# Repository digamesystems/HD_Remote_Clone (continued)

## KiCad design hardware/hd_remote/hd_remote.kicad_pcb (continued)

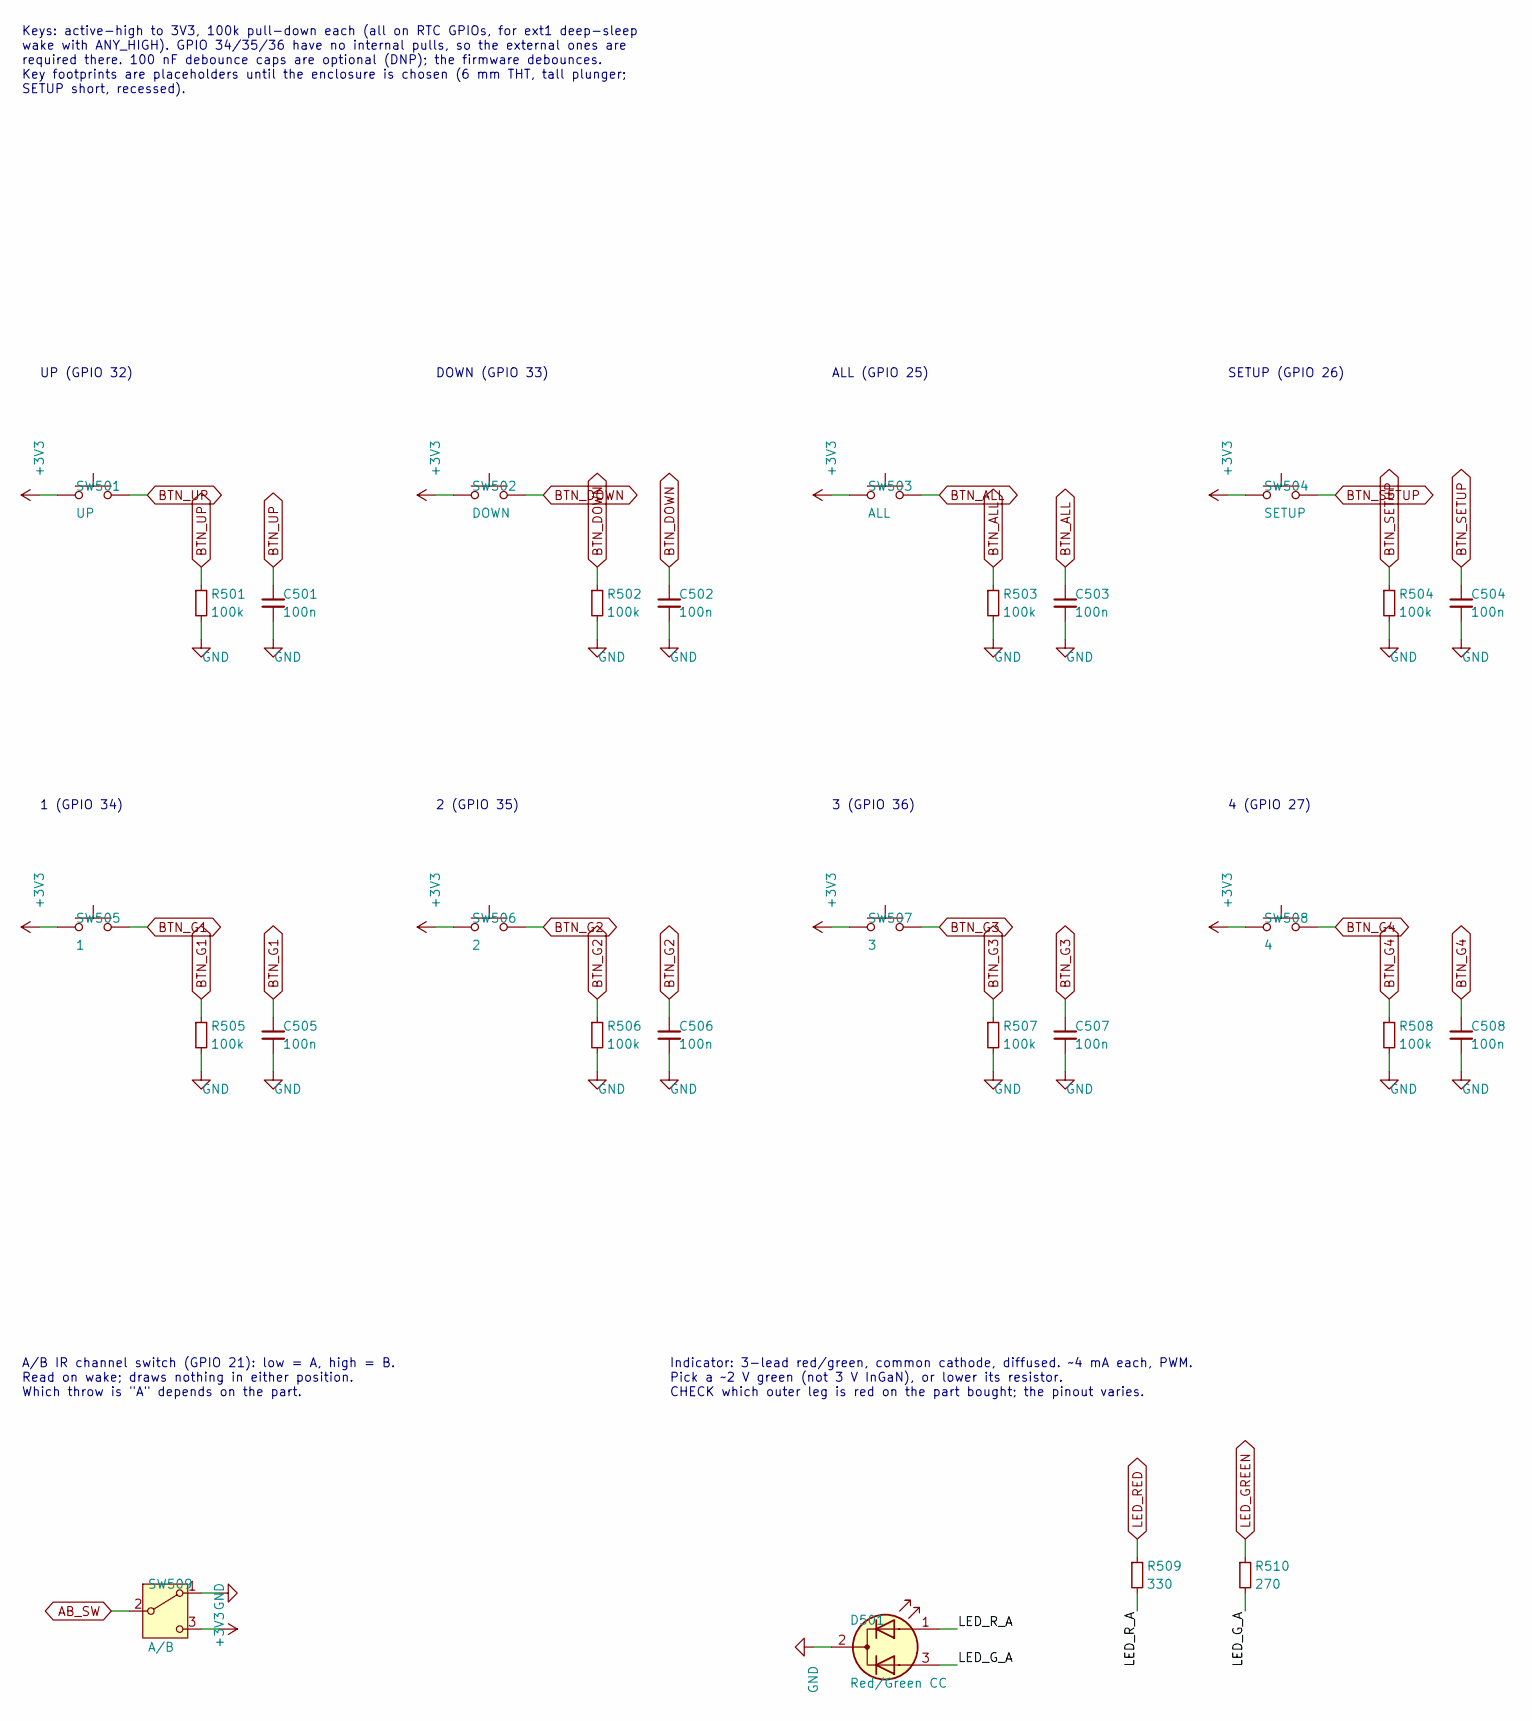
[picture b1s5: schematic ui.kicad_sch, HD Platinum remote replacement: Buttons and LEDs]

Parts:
C501, C502, C503, C504, C505, C506, C507, C508: 100n; C_0603_1608Metric; LCSC C14663
D501: Red/Green CC; LED_D5.0mm-3; MPN WP59EGW
R501, R502, R503, R504, R505, R506, R507, R508: 100k; R_0603_1608Metric; LCSC C25803
R509: 330; R_0603_1608Metric; LCSC C23138
R510: 270; R_0603_1608Metric; LCSC C22966
SW501: UP; SW_PUSH_6mm_H13mm; MPN TS02-66-130-BK-160-SCR-D
SW502: DOWN; SW_PUSH_6mm_H13mm; MPN TS02-66-130-BK-160-SCR-D
SW503: ALL; SW_PUSH_6mm_H13mm; MPN TS02-66-130-BK-160-SCR-D
SW504: SETUP; SW_PUSH_6mm_H5mm; MPN TS02-66-50-BK-160-SCR-D
SW505: 1; SW_PUSH_6mm_H13mm; MPN TS02-66-130-BK-160-SCR-D
SW506: 2; SW_PUSH_6mm_H13mm; MPN TS02-66-130-BK-160-SCR-D
SW507: 3; SW_PUSH_6mm_H13mm; MPN TS02-66-130-BK-160-SCR-D
SW508: 4; SW_PUSH_6mm_H13mm; MPN TS02-66-130-BK-160-SCR-D
SW509: A/B; SW_SPDT_PCM12; LCSC C221841

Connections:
+3V3: SW501.1, SW502.1, SW503.1, SW504.1, SW505.1, SW506.1, SW507.1, SW508.1, SW509.3 (C); also elsewhere on the board
/Buttons and LEDs/LED_G_A: D501.3 (A2), R510.2
/Buttons and LEDs/LED_R_A: D501.1 (A1), R509.2
AB_SW: SW509.2 (B); also elsewhere on the board
BTN_ALL: C503.1, R503.1, SW503.2; also elsewhere on the board
BTN_DOWN: C502.1, R502.1, SW502.2; also elsewhere on the board
BTN_G1: C505.1, R505.1, SW505.2; also elsewhere on the board
BTN_G2: C506.1, R506.1, SW506.2; also elsewhere on the board
BTN_G3: C507.1, R507.1, SW507.2; also elsewhere on the board
BTN_G4: C508.1, R508.1, SW508.2; also elsewhere on the board
BTN_SETUP: C504.1, R504.1, SW504.2; also elsewhere on the board
BTN_UP: C501.1, R501.1, SW501.2; also elsewhere on the board
GND: C501.2, C502.2, C503.2, C504.2, C505.2, C506.2, C507.2, C508.2, D501.2 (K), R501.2, R502.2, R503.2, R504.2, R505.2, R506.2, R507.2, R508.2, SW509.1 (A); also elsewhere on the board
LED_GREEN: R510.1; also elsewhere on the board
LED_RED: R509.1; also elsewhere on the board

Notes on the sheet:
A/B IR channel switch (GPIO 21): low = A, high = B. Read on wake; draws nothing in either position. Which throw is "A" depends on the part.
2 (GPIO 35)
Indicator: 3-lead red/green, common cathode, diffused. ~4 mA each, PWM. Pick a ~2 V green (not 3 V InGaN), or lower its resistor. CHECK which outer leg is red on the part bought; the pinout varies.
1 (GPIO 34)
Keys: active-high to 3V3, 100k pull-down each (all on RTC GPIOs, for ext1 deep-sleep wake with ANY_HIGH). GPIO 34/35/36 have no internal pulls, so the external ones are required there. 100 nF debounce caps are optional (DNP); the firmware debounces. Key footprints are placeholders until the enclosu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
DOWN (GPIO 33)
3 (GPIO 36)
UP (GPIO 32)
SETUP (GPIO 26)
4 (GPIO 27)
ALL (GPIO 25)

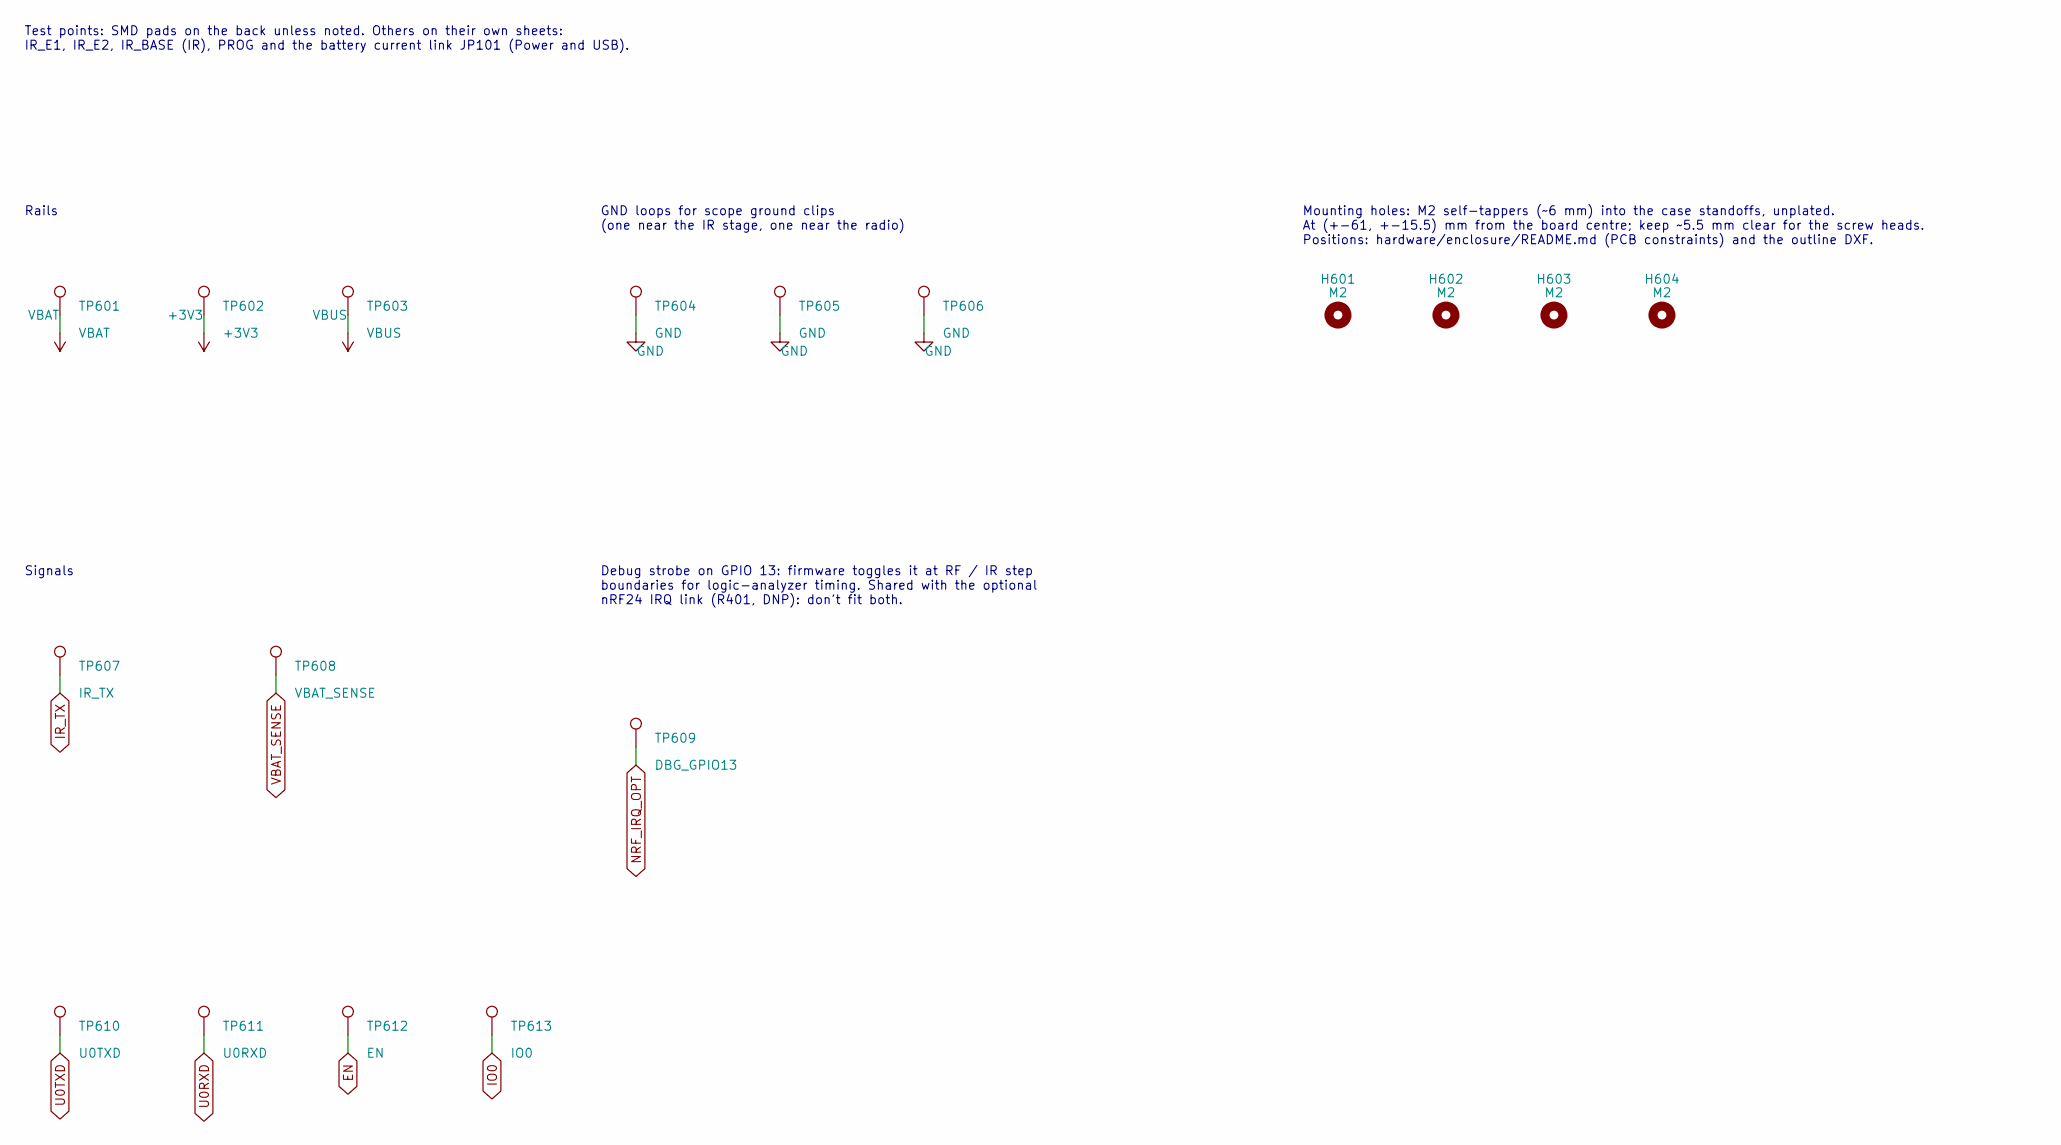
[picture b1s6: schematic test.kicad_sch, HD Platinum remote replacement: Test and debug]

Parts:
H601, H602, H603, H604: M2; MountingHole_2.2mm_M2
TP601: VBAT; TestPoint_Pad_D1.5mm
TP602: +3V3; TestPoint_Pad_D1.5mm
TP603: VBUS; TestPoint_Pad_D1.5mm
TP604, TP605, TP606: GND; TestPoint_Keystone_5000-5004_Miniature
TP607: IR_TX; TestPoint_Pad_D1.5mm
TP608: VBAT_SENSE; TestPoint_Pad_D1.5mm
TP609: DBG_GPIO13; TestPoint_Pad_D1.5mm
TP610: U0TXD; TestPoint_Pad_D1.5mm
TP611: U0RXD; TestPoint_Pad_D1.5mm
TP612: EN; TestPoint_Pad_D1.5mm
TP613: IO0; TestPoint_Pad_D1.5mm

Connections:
+3V3: TP602.1 (1_1); also elsewhere on the board
EN: TP612.1 (1_1); also elsewhere on the board
GND: TP604.1 (1_1), TP605.1 (1_1), TP606.1 (1_1); also elsewhere on the board
IO0: TP613.1 (1_1); also elsewhere on the board
IR_TX: TP607.1 (1_1); also elsewhere on the board
NRF_IRQ_OPT: TP609.1 (1_1); also elsewhere on the board
U0RXD: TP611.1 (1_1); also elsewhere on the board
U0TXD: TP610.1 (1_1); also elsewhere on the board
VBAT: TP601.1 (1_1); also elsewhere on the board
VBAT_SENSE: TP608.1 (1_1); also elsewhere on the board
VBUS: TP603.1 (1_1); also elsewhere on the board

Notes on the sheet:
Signals
GND loops for scope ground clips (one near the IR stage, one near the radio)
Debug strobe on GPIO 13: firmware toggles it at RF / IR step boundaries for logic-analyzer timing. Shared with the optional nRF24 IRQ link (R401, DNP): don't fit both.
Rails
Test points: SMD pads on the back unless noted. Others on their own sheets: IR_E1, IR_E2, IR_BASE (IR), PROG and the battery current link JP101 (Power and USB).
Mounting holes: M2 self-tappers (~6 mm) into the case standoffs, unplated. At (+-61, +-15.5) mm from the board centre; keep ~5.5 mm clear for the screw heads. Positions: hardware/enclosure/README.md (PCB constraints) and the outline DXF.

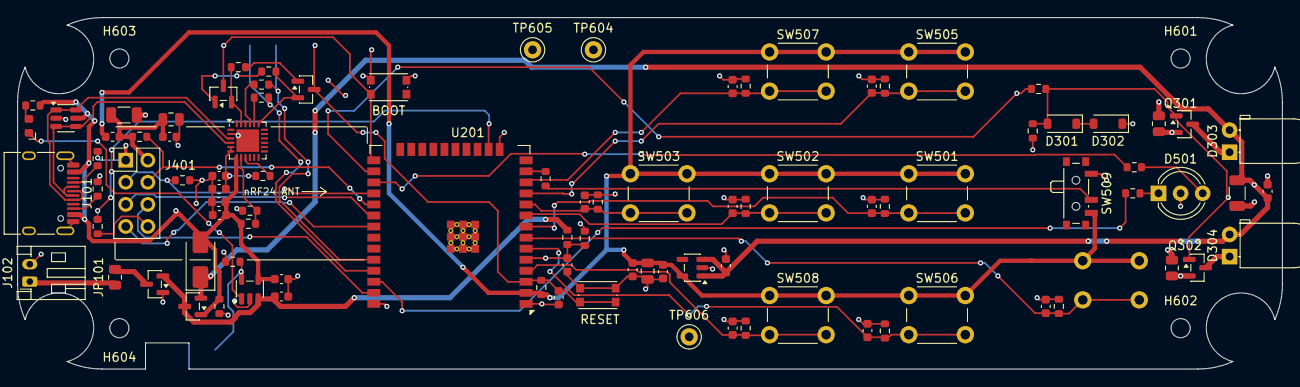
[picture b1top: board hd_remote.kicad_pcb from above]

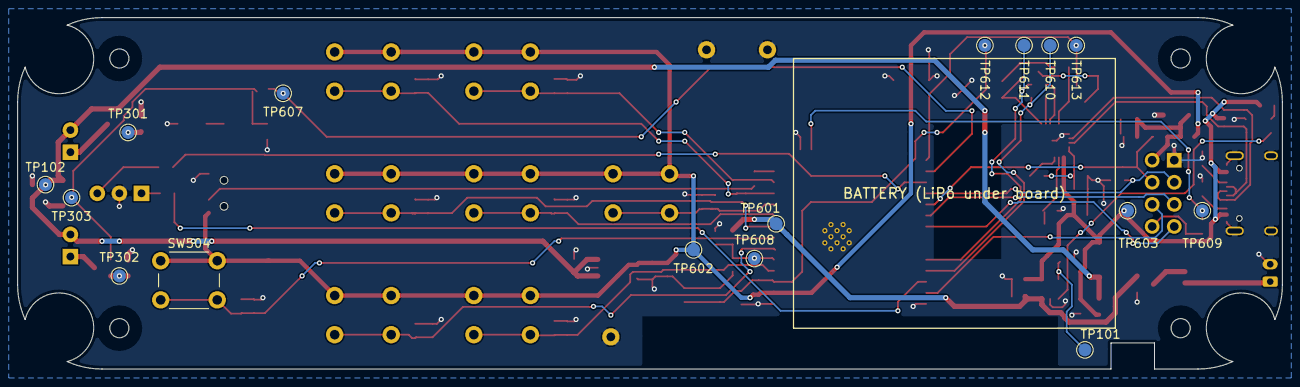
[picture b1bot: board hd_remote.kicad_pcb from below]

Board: 2 copper layers, 145.4 x 40.4 mm, 114 parts (16 on the bottom side), 57 nets.

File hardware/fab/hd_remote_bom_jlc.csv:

Comment,Designator,Footprint,LCSC Part #
4.7u,"C101,C103,C105,C106",C_0603_1608Metric,C19666
100n,"C102,C104,C109,C202,C302,C402,C501,C502,C503,C504,C505,C506,C507,C508",C_0603_1608Metric,C14663
1u,"C107,C108,C203",C_0603_1608Metric,C15849
22u,C201,C_0805_2012Metric,C45783
100u,C301,C_1206_3216Metric,C15008
10u,C401,C_0805_2012Metric,C15850
CHG,D101,LED_Kingbright_APA1606_1.6x0.6mm_Horizontal,C3034753
STPS1H100AY,D102,D_SMA,C181833
1N4148W,"D301,D302",D_SOD-123,C81598
0R (or bead),FB401,L_0603_1608Metric,C21189
USB_C_Receptacle,J101,USB_C_Receptacle_HRO_TYPE-C-31-M-12,C165948
0R,JP101,R_0805_2012Metric,C17477
MMBT3904,"Q101,Q102",SOT-23,C20526
AO3401A,"Q103,Q104",SOT-23,C15127
BC817-40,"Q301,Q302",SOT-23,C52801
5.1k,"R101,R102",R_0603_1608Metric,C23186
1k,"R103,R106,R111",R_0603_1608Metric,C21190
22k,R104,R_0603_1608Metric,C31850
47k,R105,R_0603_1608Metric,C25819
10k,"R107,R108,R109,R201,R202",R_0603_1608Metric,C25804
3.9k,R110,R_0603_1608Metric,C23018
1M,"R112,R113",R_0603_1608Metric,C22935
100k,"R114,R302,R402,R403,R501,R502,R503,R504,R505,R506,R507,R508",R_0603_1608Metric,C25803
470,R301,R_0603_1608Metric,C23179
3.3,"R303,R304",R_0805_2012Metric,C2907250
330,R509,R_0603_1608Metric,C23138
270,R510,R_0603_1608Metric,C22966
RESET/BOOT,"SW201,SW202",SW_Push_1P1T_NO_CK_KMR2,C269272
A/B,SW509,SW_SPDT_PCM12,C221841
USBLC6-2SC6,U101,SOT-23-6,C7519
CP2102N-A02-GQFN24,U102,QFN-24-1EP_4x4mm_P0.5mm_EP2.6x2.6mm,C969151
MCP73831-2-OT,U103,SOT-23-5,C424093
RT9080-33GJ5,U104,SOT-23-5,C841192
ESP32-WROOM-32E,U201,ESP32-WROOM-32E,C701341

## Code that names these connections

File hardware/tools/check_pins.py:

# SPDX-License-Identifier: GPL-2.0-or-later
"""Check the firmware's handheld pin map (include/pins.h) against the KiCad design.

Exports the schematic netlist with kicad-cli, reads which net each ESP32 module pin (U201) is on,
converts module pins to GPIO numbers, and compares that with every PIN_ constant in the
HD_BOARD_HANDHELD block of include/pins.h. Also reports ESP32 signal nets that pins.h doesn't name.

  python -I hardware/tools/check_pins.py            (from the repo root)

Exits 1 on any mismatch, so it can gate a commit. Needs KiCad 10's kicad-cli (KICAD_CLI to override).
"""
import os
import re
import subprocess
import sys
import tempfile
from pathlib import Path

sys.path.insert(0, str(Path(__file__).parent))
from sexpr import parse  # noqa: E402

ROOT = Path(__file__).resolve().parents[2]
SCH = ROOT / "hardware" / "hd_remote" / "hd_remote.kicad_sch"
PINS_H = ROOT / "include" / "pins.h"
KICAD_CLI = os.environ.get(
    "KICAD_CLI", r"C:\Users\johnp\AppData\Local\Programs\KiCad\10.0\bin\kicad-cli.exe")
MODULE = "U201"

# ESP32-WROOM-32E module pin -> GPIO (Espressif datasheet, pin layout). Power, EN, NC and the
# exposed pad are omitted.
MODULE_GPIO = {
    4: 36, 5: 39, 6: 34, 7: 35, 8: 32, 9: 33, 10: 25, 11: 26, 12: 27, 13: 14, 14: 12,
    16: 13, 23: 15, 24: 2, 25: 0, 26: 4, 27: 16, 28: 17, 29: 5, 30: 18, 31: 19, 33: 21,
    34: 3, 35: 1, 36: 22, 37: 23,
}

# pins.h constant -> the net it must be on.
EXPECTED = {
    "PIN_IR_TX": "IR_TX",
    "PIN_BTN_UP": "BTN_UP", "PIN_BTN_DN": "BTN_DOWN", "PIN_BTN_ALL": "BTN_ALL",
    "PIN_BTN_G1": "BTN_G1", "PIN_BTN_G2": "BTN_G2", "PIN_BTN_G3": "BTN_G3", "PIN_BTN_G4": "BTN_G4",
    "PIN_BTN_SETUP": "BTN_SETUP",
    "PIN_AB_SW": "AB_SW_PIN",
    "PIN_VBAT_SENSE": "VBAT_SENSE",
    "PIN_LED_RED": "LED_RED", "PIN_LED_GREEN": "LED_GREEN",
    "PIN_NRF_CSN": "NRF_CSN", "PIN_NRF_CE": "NRF_CE", "PIN_NRF_IRQ": "NRF_IRQ_OPT",
}
# Nets on fixed pins the firmware doesn't name in pins.h (SPI defaults, UART0, boot).
FIXED = {"NRF_SCK": 18, "NRF_MISO": 19, "NRF_MOSI": 23, "U0TXD": 1, "U0RXD": 3, "IO0": 0}
NOT_SIGNALS = {"GND", "+3V3", "EN"}


def short(net):
    return net.split("/")[-1]


def module_nets():
    """GPIO -> net name, from the schematic netlist."""
    with tempfile.TemporaryDirectory() as d:
        out = Path(d) / "net.net"
        subprocess.run([KICAD_CLI, "sch", "export", "netlist", "--format", "kicadsexpr",
                        "-o", str(out), str(SCH)], check=True, capture_output=True)
        tree = parse(out.read_text(encoding="utf-8"))
    root = tree[0] if isinstance(tree[0], list) else tree
    nets = next(x for x in root if isinstance(x, list) and x and x[0] == "nets")
    gpio_net = {}
    for net in nets[1:]:
        name = next(x[1] for x in net if isinstance(x, list) and x[0] == "name")
        for node in (x for x in net if isinstance(x, list) and x[0] == "node"):
            f = {x[0]: x[1] for x in node[1:] if isinstance(x, list) and len(x) > 1}
            if f.get("ref") == MODULE and f.get("pin", "").isdigit():
                pin = int(f["pin"])
                if pin in MODULE_GPIO:
                    gpio_net[MODULE_GPIO[pin]] = short(name)
    return gpio_net


def handheld_pins():
    """PIN_ name -> GPIO from the HD_BOARD_HANDHELD block of pins.h (PIN_NONE skipped)."""
    text = PINS_H.read_text(encoding="utf-8")
    m = re.search(r"#if defined\(HD_BOARD_HANDHELD\)(.*?)#else", text, re.S)
    if not m:
        sys.exit("pins.h: no HD_BOARD_HANDHELD block found")
    pins = {}
    for name, value in re.findall(r"constexpr\s+uint8_t\s+(PIN_\w+)\s*=\s*(\w+)\s*;", m.group(1)):
        if value.isdigit():
            pins[name] = int(value)
    return pins


def main():
    gpio_net = module_nets()
    pins = handheld_pins()
    fails, lines = [], []

    for name, net in EXPECTED.items():
        if name not in pins:
            fails.append(f"{name}: missing from the handheld block of pins.h (net {net})")
            continue
        got = gpio_net.get(pins[name], "(not connected)")
        line = f"{name:15s} GPIO {pins[name]:2d}  net {got}"
        if got != net:
            fails.append(f"{name} = GPIO {pins[name]} is on net {got}, expected {net}")
            line += f"   <-- expected {net}"
        lines.append(line)
    for name in sorted(set(pins) - set(EXPECTED)):
        fails.append(f"{name} = GPIO {pins[name]}: not in this script's EXPECTED table (add it)")

    for net, gpio in FIXED.items():
        got = gpio_net.get(gpio, "(not connected)")
        if got != net:
            fails.append(f"fixed pin GPIO {gpio} is on net {got}, expected {net}")

    named = set(EXPECTED.values()) | set(FIXED)
    for gpio, net in sorted(gpio_net.items()):
        if net in NOT_SIGNALS or net.startswith("unconnected") or net in named:
            continue
        fails.append(f"GPIO {gpio} is on net {net}, which pins.h doesn't name")

    print("\n".join(lines))
    if fails:
        print("\nFAIL:\n  " + "\n  ".join(fails))
        sys.exit(1)
    print(f"\nok: {len(EXPECTED)} pins.h constants and {len(FIXED)} fixed pins match the schematic")


if __name__ == "__main__":
    main()

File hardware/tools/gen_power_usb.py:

# SPDX-License-Identifier: GPL-2.0-or-later
"""Generates hardware/hd_remote/power_usb.kicad_sch (first draft) from
docs/HARDWARE.md: USB-C, ESD, CP2102N with auto-reset, LiPo charger, 3.3 V LDO,
battery sense. Run once; after editing the sheet in KiCad, don't rerun.

    python -I hardware/tools/gen_power_usb.py
"""

import os
import sys

sys.path.insert(0, os.path.dirname(os.path.abspath(__file__)))
import schgen  # noqa: E402

HERE = os.path.dirname(os.path.abspath(__file__))
PROJ_DIR = os.path.join(HERE, "..", "hd_remote")
ROOT = os.path.join(PROJ_DIR, "hd_remote.kicad_sch")
OUT = os.path.join(PROJ_DIR, "power_usb.kicad_sch")
PROJECT = "hd_remote"
SHEET_UUID = "2b0f6c1e-5d3a-4f7e-8a21-6c9d0e3f4a10"

R = "Resistor_SMD:R_0603_1608Metric"
C = "Capacitor_SMD:C_0603_1608Metric"
GLOBAL = ("EN", "IO0", "U0TXD", "U0RXD", "VBAT_SENSE")


def res(s, value, gx, gy, top, bottom, note=""):
    f = {"Footprint": R}
    if note:
        f["Description"] = note
    return s.part("Device:R_Small", "R", value, gx, gy, {"1": top, "2": bottom}, f, GLOBAL)


def cap(s, value, gx, gy, top, bottom):
    return s.part("Device:C_Small", "C", value, gx, gy, {"1": top, "2": bottom}, {"Footprint": C}, GLOBAL)


def build():
    s = schgen.Sheet(PROJECT, "power_usb.kicad_sch", "Power and USB", schgen.root_uuid(ROOT), SHEET_UUID,
                     ref_base=100)

    # --- USB-C receptacle (sink), CC pull-downs, ESD ---
    s.text("USB-C (USB 2.0, sink): 5.1k on CC1/CC2, USBLC6 on D+/D-", 8, 12)
    s.part("Connector:USB_C_Receptacle_USB2.0_16P", "J", "USB_C_Receptacle", 16, 32, {
        "A1": "GND", "A12": "GND", "B1": "GND", "B12": "GND", "SH": "GND",
        "A4": "VBUS", "A9": "VBUS", "B4": "VBUS", "B9": "VBUS",
        "A5": "CC1", "B5": "CC2",
        "A6": "USB_DP", "B6": "USB_DP", "A7": "USB_DN", "B7": "USB_DN",
        "A8": None, "B8": None,
    }, {"Footprint": "Connector_USB:USB_C_Receptacle_HRO_TYPE-C-31-M-12"}, GLOBAL)
    res(s, "5.1k", 30, 30, "CC1", "GND")
    res(s, "5.1k", 34, 30, "CC2", "GND")
    s.part("Power_Protection:USBLC6-2SC6", "U", "USBLC6-2SC6", 46, 32, {
        "1": "USB_DP", "6": "USB_DP", "3": "USB_DN", "4": "USB_DN", "5": "VBUS", "2": "GND",
    }, None, GLOBAL)

    # --- CP2102N USB-UART, bus-powered (VBUS only, draws nothing from the battery) ---
    s.text("CP2102N: powered from VBUS only. VBUS sense divider as on the CP2102N-EK.\n"
           "1k in series on TXD/RXD limits back-powering when USB is unplugged (verify sleep current).",
           60, 4)
    s.part("Interface_USB:CP2102N-Axx-xQFN24", "U", "CP2102N-A02-GQFN24", 80, 36, {
        "3": "USB_DP", "4": "USB_DN", "8": "CP_VBUS", "9": "CP_RST",
        "7": "VBUS", "6": "VDD_USB", "5": "VDD_USB", "2": "GND", "25": "GND",
        "21": "CP_TXD", "20": "CP_RXD", "23": "DTR", "19": "RTS",
        "1": None, "10": None, "11": None, "12": None, "13": None, "14": None,
        "15": None, "16": None, "17": None, "18": None, "22": None, "24": None,
    }, None, GLOBAL)
    cap(s, "4.7u", 62, 12, "VBUS", "GND")        # VREGIN bulk
    cap(s, "100n", 66, 12, "VBUS", "GND")        # VREGIN
    cap(s, "1u", 70, 12, "VDD_USB", "GND")       # VDD / VIO
    cap(s, "100n", 74, 12, "VDD_USB", "GND")
    res(s, "1k", 78, 12, "VDD_USB", "CP_RST", "RST pull-up to VIO (verify value)")
    res(s, "22.1k", 84, 12, "VBUS", "CP_VBUS", "VBUS sense divider, top")
    res(s, "47.5k", 88, 12, "CP_VBUS", "GND", "VBUS sense divider, bottom")
    res(s, "1k", 104, 28, "CP_TXD", "U0RXD", "Series: CP2102N TXD -> ESP32 RX0 (GPIO 3)")
    res(s, "1k", 108, 28, "U0TXD", "CP_RXD", "Series: ESP32 TX0 (GPIO 1) -> CP2102N RXD")

    # --- Auto-reset (DevKitC circuit): DTR/RTS -> EN / IO0 ---
    s.text("Auto-reset, as on the ESP32-DevKitC", 116, 20)
    res(s, "10k", 118, 30, "DTR", "Q1_B")
    s.part("Transistor_BJT:MMBT3904", "Q", "MMBT3904", 124, 30,
           {"1": "Q1_B", "2": "RTS", "3": "EN"}, None, GLOBAL)
    res(s, "10k", 118, 42, "RTS", "Q2_B")
    s.part("Transistor_BJT:MMBT3904", "Q", "MMBT3904", 124, 42,
           {"1": "Q2_B", "2": "DTR", "3": "IO0"}, None, GLOBAL)

    # --- LiPo charger ---
    s.text("Charger: MCP73831, ~250 mA (R_PROG 4.02k). Charge LED from VBUS, lit while charging.\n"
           "Load runs straight from VBAT (no power path).", 4, 66)
    s.part("Battery_Management:MCP73831-2-OT", "U", "MCP73831-2-OT", 20, 78,
           {"4": "VBUS", "2": "GND", "5": "PROG", "1": "STAT", "3": "VBAT"}, None, GLOBAL)
    cap(s, "4.7u", 8, 78, "VBUS", "GND")
    cap(s, "4.7u", 34, 78, "VBAT", "GND")
    res(s, "4.02k", 12, 90, "PROG", "GND", "I_charge = 1000 V / R_PROG = ~250 mA")
    s.text("TP: V(PROG) = 1 V at full\ncharge current (~250 mA)", 18, 96)
    s.part("Connector:TestPoint", "TP", "PROG", 20, 92, {"1": "PROG"},
           {"Footprint": "TestPoint:TestPoint_Pad_D1.5mm"}, GLOBAL)
    s.part("Device:LED_Small", "D", "CHG", 42, 78, {"1": "STAT", "2": "LED_CHG"},
           {"Footprint": "LED_SMD:LED_0603_1608Metric", "Description": "Charge LED (red or orange)"},
           GLOBAL)
    res(s, "1k", 48, 78, "VBUS", "LED_CHG")

    # --- Battery connector ---
    s.text("LiPo, 1 cell, protected. Polarity: mark + and - on the silkscreen at J102;\n"
           "Q103 blocks a reversed cell. Still check the cell's lead colours.", 54, 68)
    s.part("Connector_Generic:Conn_01x02", "J", "Battery", 62, 78, {"1": "VBAT_BATT", "2": "GND"},
           {"Footprint": "Connector_JST:JST_PH_S2B-PH-K_1x02_P2.00mm_Horizontal"}, GLOBAL)
    s.text("Battery current link: cut the bridge and put a uA meter\n"
           "across the pads to measure total battery current\n"
           "(sleep target ~11-16 uA). Re-bridge with solder after.", 50, 96)
    s.part("Jumper:SolderJumper_2_Bridged", "JP", "I_BAT", 58, 92, {"1": "VBAT_BATT", "2": "VBAT_JP"},
           {"Footprint": "Jumper:SolderJumper-2_P1.3mm_Bridged_RoundedPad1.0x1.5mm"}, GLOBAL)

    # --- 3.3 V LDO ---
    s.text("LDO: RT9080-33GJ5 (2 uA Iq). Symbol is the AP2112K's: same SOT-23-5 pinout\n"
           "(1 VIN, 2 GND, 3 EN, 4 NC, 5 VOUT). Verify against the RT9080 datasheet.", 70, 66)
    s.part("Regulator_Linear:AP2112K-3.3", "U", "RT9080-33GJ5", 80, 78,
           {"1": "VBAT", "3": "VBAT", "2": "GND", "4": None, "5": "+3V3"}, None, GLOBAL)
    cap(s, "1u", 72, 88, "VBAT", "GND")
    cap(s, "1u", 88, 88, "+3V3", "GND")

    # --- Battery sense ---
    s.text("Battery sense to GPIO 39 (ADC1_CH3): VBAT / 2, ~2 uA", 96, 94)
    res(s, "1M", 100, 78, "VBAT", "VBAT_SENSE")
    res(s, "1M", 104, 78, "VBAT_SENSE", "GND")
    cap(s, "100n", 108, 78, "VBAT_SENSE", "GND")

    # --- Reverse-polarity protection (placed last so earlier references keep their numbers) ---
    s.text("Reverse-polarity protection: P-MOSFET in the battery lead, gate to GND.\n"
           "Cell the right way round: the body diode lifts S, Vgs ~ -VBAT, the FET turns on\n"
           "(~50-80 mohm, ~20 mV at 300 mA) and the charger can still charge through it.\n"
           "Cell reversed: Vgs = 0 and the body diode is reverse-biased, so nothing flows.", 80, 100)
    s.part("Transistor_FET:AO3401A", "Q", "AO3401A", 40, 104,
           {"1": "GND", "2": "VBAT", "3": "VBAT_JP"},
           {"Description": "Reverse-polarity protection; any SOT-23 P-FET with |Vgs(th)| < ~1.5 V, Vgs max >= 8 V"},
           GLOBAL)

    # --- Power flags: the connectors' power pins are passive, and the symbol
    # marks the CP2102N's VDD (its regulator output) as an input. VBAT needs
    # none: the charger's VBAT pin is a power output.
    s.flag("VBUS", 116, 90)
    s.flag("GND", 124, 90)
    s.flag("VDD_USB", 134, 90)

    text = s.render({
        "title": "HD Platinum remote replacement: Power and USB",
        "date": "2026-11-12",
        "rev": "0.1",
        "comments": ["Draft, generated by hardware/tools/gen_power_usb.py", "Spec: docs/HARDWARE.md"],
    })
    with open(OUT, "w", encoding="utf-8", newline="\n") as f:
        f.write(text)
    added = schgen.add_sheet_to_root(ROOT, PROJECT, SHEET_UUID, "Power and USB", "power_usb.kicad_sch",
                                     2, 10, 10)
    print("wrote", OUT, "| root sheet block", "added" if added else "already present")
    nets = {}
    for ref, pin, net in s.netlist:
        nets.setdefault(net, []).append("%s.%s" % (ref, pin))
    for net in sorted(nets, key=lambda n: (n is None, str(n))):
        print("  %-12s %s" % (net, " ".join(nets[net])))


if __name__ == "__main__":
    build()
